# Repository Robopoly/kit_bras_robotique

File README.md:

# Kit Bras Robotique

The Kit Bras Robotique is a wireless robotic arm kit designed by [Robopoly](https://www.epfl.ch/campus/associations/robopoly/), the student makerspace of EPFL. A handheld controller with two joysticks drives a 3D printed arm with five servos.

Robopoly members buy the kit as separate parts and solder it themselves at the workshop, with help from the committee. It is an advanced kit: it uses small surface-mount components, so soldering experience is recommended but not required.

> **About the name:** this kit used to be called "Kit JIG". The boards, the assembly guides and parts of the code still use that name. It is now only used for another kit, with a wired controller and an Arduino Nano, which is in the [JIG repository](https://github.com/Robopoly/JIG). The mechanical arm is the same in both kits.

## Features

- Two boards, each with an ESP32-S3 module programmed over USB-C
- Wireless link between the controller and the arm (ESP-NOW, no WiFi network needed)
- Controller powered over USB-C or by an 18650 battery, with charger and battery protection on the board
- Arm board with 5 servo connectors (SG90 or MG90 servos) and a DC jack
- Optional Console extension: OLED screen, vibration motors, extra buttons and mini-games

## Repository contents

| Folder | Content |
|---|---|
| [`docs/`](docs) | Assembly guides, schematics, images |
| [`firmware/arm/`](firmware/arm) | Program of the arm board |
| [`firmware/controller_basic/`](firmware/controller_basic) | Program of the controller **without** the Console extension |
| [`firmware/controller_console/`](firmware/controller_console) | Program of the controller **with** the Console extension |
| [`firmware/tests/`](firmware/tests) | Test program used during assembly |
| [`hardware/`](hardware) | KiCad projects, Gerber files and bills of materials of both boards |
| [`mechanical/`](mechanical) | 3D printed parts (STL to print, STEP to modify) |
| [`tools/space_invaders_simulator/`](tools/space_invaders_simulator) | Space Invaders simulator for PC (Python) |

## Building the kit

The guides are in French for now. Do not move on until each test passes.

| Step | Guide | Test |
|---|---|---|
| 1. Controller board | [Controller guide](docs/controller_assembly_guide_v1.pdf) | The blue LED lights up, the board is detected over USB, `01_melody` plays a melody, both charger LEDs light up |
| 2. Arm board | [Arm board guide](docs/arm_assembly_guide_v1.pdf) | The LED lights up, the board is detected over USB |
| 3. Mechanical arm | [Mechanical guide](docs/arm_mechanical_guide_fsrm.pdf), pages 4 to 8 | |
| 4. Programs and pairing | [Programming](#programming) | The joysticks move the arm |

**Before you insert the battery, ask someone from the committee to check your controller.**

### Corrections to the guides

Some values in the soldering guides do not match the schematics. The values below come from the KiCad files:

| Board | Reference | In the guide | Use |
|---|---|---|---|
| Controller | R5, R6 | 1 kΩ | **10 kΩ** |
| Controller | R11 | 1 kΩ | **1.2 kΩ** |
| Controller | R18 | 1.2 kΩ | **1 kΩ** |
| Controller | C12 | 10 µF | **100 nF** |
| Controller | R16, R17 | 20 kΩ | **10 kΩ** |
| Controller | L1 | 10 µH | To be confirmed: 4.7 µH in the schematic, 10 µH on the PCB |
| Arm | R3 | 75 Ω | To be confirmed: 1 kΩ in the schematic, 75 Ω on the PCB |

If you have a doubt about a part, ask the committee.

### Which side of the board?

Both sides are used, and the guides do not always say which one.

| Board | Top side | Bottom side |
|---|---|---|
| Controller | U1, U6, U7, U8, Q1, L1, D5 to D8, C1 to C15, R1 to R6, R9 to R17, joysticks (U3, U4), buttons (S1, S2), buzzer (LS1) | U2 (ESP32), U9, D1, Q3, R7, R8, R18, USB-C (J1), switch (U5), battery holder (BT1) |
| Arm | U1, U2 (ESP32), D5, buttons (S1, S2), USB-C (J1), DC jack (J2), switch (U3), servo connectors (M1 to M5) | U9, D1, C1 to C10, R1 to R6 |

The components of the Console extension are J2, J3 and J4 (top), and M1, M2, Q2, Q4, D2, D3, R19 and R20 (bottom). The guide of this extension is not written yet. In the schematic and in the bill of materials, M1 and M2 are called J5 and J6.

### Mechanical arm

The mechanical guide was written for the Kit JIG workshops. Only pages 4 to 8 apply to this kit: the controller, the board and the wiring described on the other pages are different. Print these parts:

| File | Number in the guide | Quantity |
|---|---|---|
| `base` | 1 | 1 |
| `rotating_base` | 2 | 1 |
| `arm1` | 3 | 1 |
| `arm1_servo` | 4 | 1 |
| `arm2_servo` | 5 | 1 |
| `arm2` | 6 | 1 |
| `servo_support` | 7 | 1 |
| `gripper_base` | 8 | 1 |
| `rack` | 9 | **2** |
| `pinion` | 10 | 1 |

You also need the screws that come with the servos and M2x8 screws.

## Power

| Board | Switch | Positions |
|---|---|---|
| Controller | U5 | Cable (USB-C) or Batt (battery) |
| Arm | U3 | USB or Jack |

- **The DC jack of the arm goes straight to the servos: use a 5 V supply only.** The board has no protection against reversed polarity. *To be completed: which supply to use, and its polarity.*
- **Do not move the arm on USB power.** Five servos can draw several amps. Use the USB position to program the board, and the Jack position to move the arm.
- **When the arm is powered up, all the servos move straight to 90°.**

## Programming

### Download mode

If the board is not detected, or keeps connecting and disconnecting: hold **GPIO0**, press and release **RESET**, then release GPIO0. Press RESET again to start the program after the upload.

### Test program

Open [`01_melody`](firmware/tests/01_melody/01_melody.ino) with the [Arduino IDE](https://www.arduino.cc/en/software), with the **esp32 by Espressif Systems** package and the board **ESP32S3 Dev Module**. It plays a melody on the buzzer of the controller.

### Main programs

The main programs use [VS Code](https://code.visualstudio.com/) with the **PlatformIO IDE** extension. Open the folder of the program, plug in the board and click **Upload**.

| Board | Folder |
|---|---|
| Arm | [`firmware/arm/`](firmware/arm) |
| Controller without screen | [`firmware/controller_basic/`](firmware/controller_basic) |
| Controller with the Console extension | [`firmware/controller_console/`](firmware/controller_console) |

### Pairing the two boards

Each board needs the MAC address of the other one. The addresses in the code belong to the boards of the designer, so **you must replace them with yours**. Follow the steps in the [README of the arm program](firmware/arm/README.md#configuring-mac-addresses-required). If the Serial Monitor stays empty, see [Known issues](#known-issues).

### Controls

| Control | Action |
|---|---|
| Joystick 1 horizontal / vertical | Base / shoulder |
| Joystick 2 vertical / horizontal | Elbow / wrist |
| Joystick 2 button | Open or close the gripper |
| Joystick 1 button | `controller_basic`: back to the rest position. `controller_console`: back to the menu |

## Pinout

| Controller GPIO | Function |
|---|---|
| 1, 2, 5 | Joystick 1: vertical, horizontal, button |
| 3, 4, 6 | Joystick 2: vertical, horizontal, button |
| 8, 9 | Screen (J3): SDA, SCL |
| 10 | Battery voltage divided by 2 |
| 12 | Buzzer |
| 17, 18 | Vibration motors M1, M2 |
| 35 to 38, 39 to 42 | Extra buttons: J2, J4 |
| 0 | GPIO0 button |

| Arm GPIO | Function |
|---|---|
| 1 to 5 | Servos M1 to M5: base, shoulder, elbow, wrist, gripper |
| 0 | GPIO0 button |

Pinout of the servo connectors: pin 1 is the signal, pin 2 is 5 V and pin 3 is GND. The full wiring is in the schematics of the [controller](docs/controller_schematic_v1.pdf) and of the [arm board](docs/arm_schematic_v1.pdf).

## Known issues

These issues were found by reading the code and the PCB files. They have not been checked on a real board yet.

- **The Serial Monitor may stay empty.** Both boards only have the native USB of the ESP32-S3, and the programs do not enable it for the Serial Monitor. Workaround (it compiles, but is not tested on a board): add `-DARDUINO_USB_CDC_ON_BOOT=1` to `build_flags` in `platformio.ini`, then upload again.
- **The arm has no status LED.** The program uses GPIO 8, which is not connected. The LED D5 only shows that the board is powered. Ignore the status LED in the READMEs.
- **The joystick buttons may act when released**, because the code expects the opposite wiring. With `controller_basic`, the gripper may also move at startup.
- **The extra buttons of the Console extension are not used** by the programs yet.
- **"DOOM (Ecran)"** needs a separate screen whose program is not in this repository.
- **The README of the arm program** describes an external supply wired by hand. This board has a DC jack instead.

## To be completed

- Power supply of the arm
- Guide and part references of the Console extension
- Mechanical guide for this kit, print settings
- Memory variant of the ESP32-S3 modules
- Supplier references in the bills of materials
- Photos of the assembled kit: the board images above are renders, with several parts missing and not the real colors

## Hardware files

The KiCad projects are in [`hardware/controller/kicad/`](hardware/controller/kicad) and [`hardware/arm/kicad/`](hardware/arm/kicad). Open the `.kicad_pro` files with KiCad 10 or later. The Gerber files (`gerber_v1.zip`) were exported on 17 March 2026.

## Links

- [Kit page](https://www.epfl.ch/campus/associations/robopoly/kits/kit-jig-bras-robotique-telecommande/) (in French)
- [Robopoly](https://www.epfl.ch/campus/associations/robopoly/), workshop BM 9139, EPFL
- Contact: [robopoly@epfl.ch](mailto:robopoly@epfl.ch)

## License

Boards and programs designed by Sonny Basso for Robopoly.

- The three main programs (`firmware/arm`, `firmware/controller_basic` and `firmware/controller_console`) and the simulator (`tools/space_invaders_simulator`) are under the MIT license. See the `LICENSE` file in each folder.
- Everything else is published by Robopoly under the [Creative Commons Attribution-NonCommercial-ShareAlike 4.0](LICENSE.txt) license.

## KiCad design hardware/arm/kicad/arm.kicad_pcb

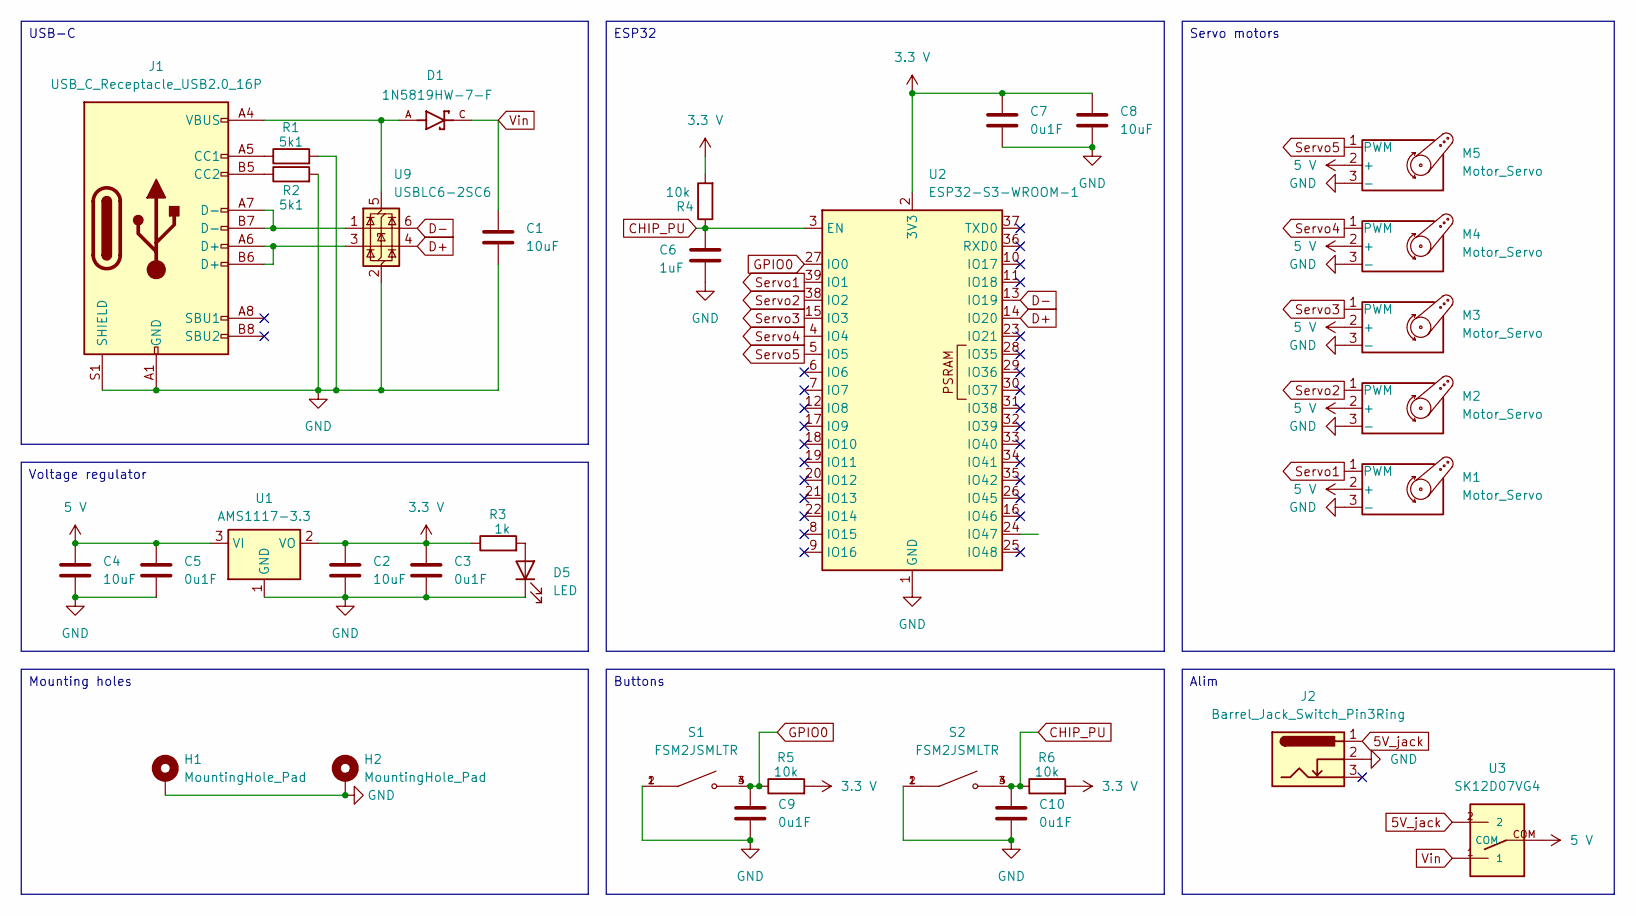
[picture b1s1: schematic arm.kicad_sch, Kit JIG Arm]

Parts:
C1, C2, C4, C8: 10uF; C_0805_2012Metric_Pad1.18x1.45mm_HandSolder
C3, C5, C7, C9, C10: 0u1F; C_0805_2012Metric_Pad1.18x1.45mm_HandSolder
C6: 1uF; C_0805_2012Metric_Pad1.18x1.45mm_HandSolder
D1: 1N5819HW-7-F; SOD3715X145N; PARTREV 18-2
D5: LED; LED_0805_2012Metric_Pad1.15x1.40mm_HandSolder
H1, H2: MountingHole_Pad; MountingHole_2.2mm_M2_ISO14580_Pad_TopBottom
J1: USB_C_Receptacle_USB2.0_16P; USB_C_Receptacle_HRO_TYPE-C-31-M-12
J2: Barrel_Jack_Switch_Pin3Ring; BarrelJack_Wuerth_6941xx301002
M1, M2, M3, M4, M5: Motor_Servo; PinHeader_1x03_P2.54mm_Vertical
R1, R2: 5k1; R_0805_2012Metric_Pad1.20x1.40mm_HandSolder
R3: 1k; R_0805_2012Metric_Pad1.20x1.40mm_HandSolder
R4, R5, R6: 10k; R_0805_2012Metric_Pad1.20x1.40mm_HandSolder
S1, S2: FSM2JSMLTR; SW_1571527-2; PARTREV V
U1: AMS1117-3.3; SOT-223-3_TabPin2
U2: ESP32-S3-WROOM-1
U3: SK12D07VG4
U9: USBLC6-2SC6; SOT-23-6

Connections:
3.3 V: C2.1, C3.1, C7.1, C8.1, R3.1, R4.2, R5.2, R6.2, U1.2 (VO), U2.2 (3V3)
5 V: C4.1, C5.1, M1.2 (+), M2.2 (+), M3.2 (+), M4.2 (+), M5.2 (+), U1.3 (VI), U3.COM
5V_jack: J2.1, U3.2
CHIP_PU: C6.1, C10.1, R4.1, R6.1, S2.3, S2.4, U2.3 (EN)
D+: U2.14 (IO20), U9.4 (I/O2)
D-: U2.13 (IO19), U9.6 (I/O1)
GND: C1.2, C2.2, C3.2, C4.2, C5.2, C6.2, C7.2, C8.2, C9.2, C10.2, D5.1 (K), H1.1, H2.1, J1.A1 (GND), J1.A12 (GND), J1.B1 (GND), J1.B12 (GND), J1.S1 (SHIELD), J2.2, M1.3 (-), M2.3 (-), M3.3 (-), M4.3 (-), M5.3 (-), R1.2, R2.2, S1.1, S1.2, S2.1, S2.2, U1.1 (GND), U2.1 (GND), U2.40 (GND), U2.41 (GND), U9.2 (GND)
GPIO0: C9.1, R5.1, S1.3, S1.4, U2.27 (IO0)
unnamed: D5.2 (A), R3.2
unnamed: J1.A5 (CC1), R1.1
unnamed: J1.B5 (CC2), R2.1
unnamed: J1.A6 (D+), J1.B6 (D+), U9.3 (I/O2)
unnamed: J1.A7 (D-), J1.B7 (D-), U9.1 (I/O1)
unnamed: D1.A, J1.A4 (VBUS), J1.A9 (VBUS), J1.B4 (VBUS), J1.B9 (VBUS), U9.5 (VBUS)
Servo1: M1.1 (PWM), U2.39 (IO1)
Servo2: M2.1 (PWM), U2.38 (IO2)
Servo3: M3.1 (PWM), U2.15 (IO3)
Servo4: M4.1 (PWM), U2.4 (IO4)
Servo5: M5.1 (PWM), U2.5 (IO5)
Vin: C1.1, D1.C, U3.1

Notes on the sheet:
Servo motors
Mounting holes
USB-C
Voltage regulator
ESP32
Buttons
Alim

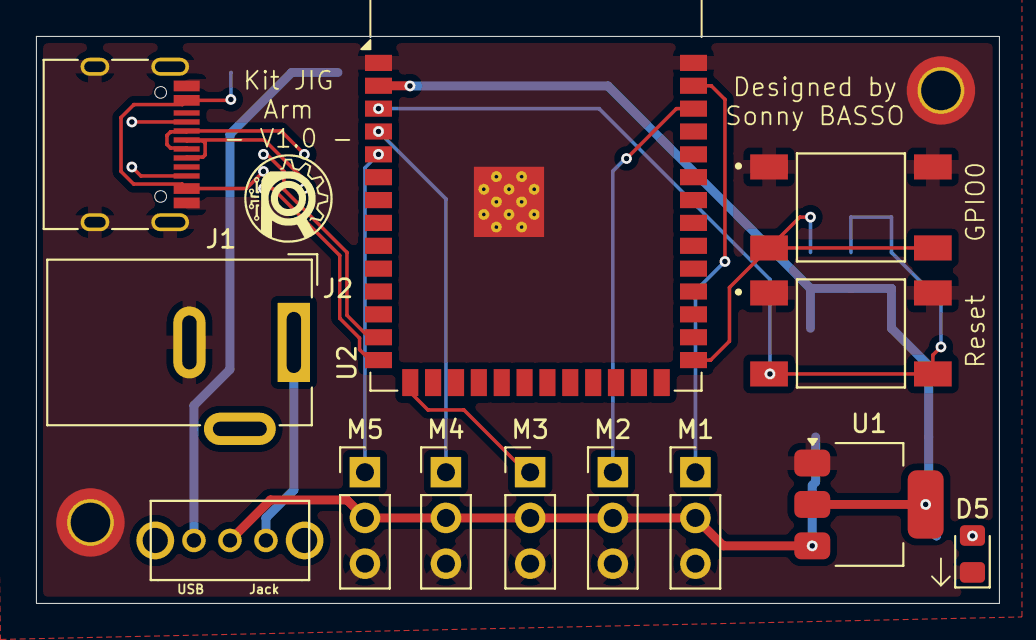
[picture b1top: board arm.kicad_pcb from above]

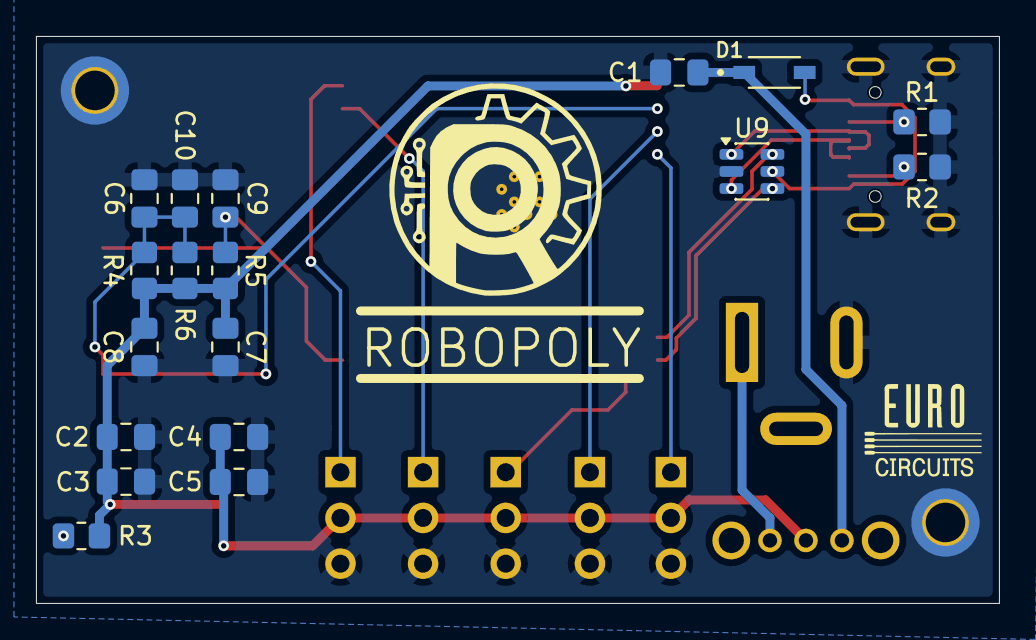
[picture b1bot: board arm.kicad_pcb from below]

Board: 2 copper layers, 53.5 x 31.5 mm, 33 parts (18 on the bottom side), 20 nets.

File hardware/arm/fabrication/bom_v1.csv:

"Reference","Qty","Value","DNP","Footprint","Datasheet"
"C1,C2,C4,C8","4","10uF","","Capacitor_SMD:C_0805_2012Metric_Pad1.18x1.45mm_HandSolder",""
"C3,C5,C7,C9,C10","5","0u1F","","Capacitor_SMD:C_0805_2012Metric_Pad1.18x1.45mm_HandSolder",""
"C6","1","1uF","","Capacitor_SMD:C_0805_2012Metric_Pad1.18x1.45mm_HandSolder",""
"D1","1","1N5819HW-7-F","","1N5819HW-7-F:SOD3715X145N",""
"D5","1","LED","","LED_SMD:LED_0805_2012Metric_Pad1.15x1.40mm_HandSolder",""
"J1","1","USB_C_Receptacle_USB2.0_16P","","Connector_USB:USB_C_Receptacle_HRO_TYPE-C-31-M-12","https://www.usb.org/sites/default/files/documents/usb_type-c.zip"
"J2","1","Barrel_Jack_Switch_Pin3Ring","","Connector_BarrelJack:BarrelJack_Wuerth_6941xx301002",""
"M1,M2,M3,M4,M5","5","Motor_Servo","","Connector_PinHeader_2.54mm:PinHeader_1x03_P2.54mm_Vertical","http://forums.parallax.com/uploads/attachments/46831/74481.png"
"R1,R2","2","5k1","","Resistor_SMD:R_0805_2012Metric_Pad1.20x1.40mm_HandSolder",""
"R3","1","1k","","Resistor_SMD:R_0805_2012Metric_Pad1.20x1.40mm_HandSolder",""
"R4,R5,R6","3","10k","","Resistor_SMD:R_0805_2012Metric_Pad1.20x1.40mm_HandSolder",""
"S1,S2","2","FSM2JSMLTR","","FSM2JSMLTR:SW_1571527-2",""
"U1","1","AMS1117-3.3","","Package_TO_SOT_SMD:SOT-223-3_TabPin2","http://www.advanced-monolithic.com/pdf/ds1117.pdf"
"U2","1","ESP32-S3-WROOM-1","","RF_Module:ESP32-S3-WROOM-1","https://www.espressif.com/sites/default/files/documentation/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"
"U3","1","SK12D07VG4","","SK12D07VG4:SK12D07VG4",""
"U9","1","USBLC6-2SC6","","Package_TO_SOT_SMD:SOT-23-6","https://www.st.com/resource/en/datasheet/usblc6-2.pdf"

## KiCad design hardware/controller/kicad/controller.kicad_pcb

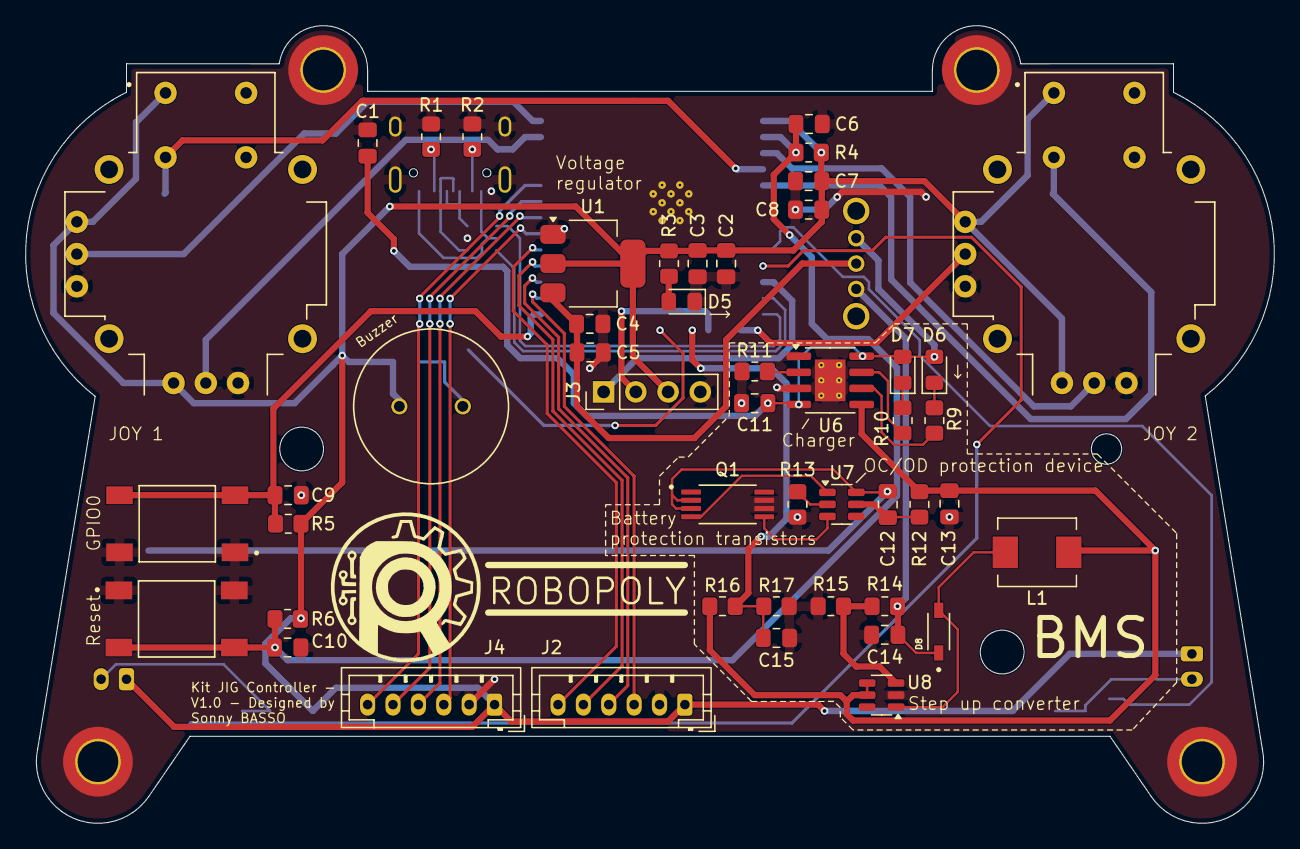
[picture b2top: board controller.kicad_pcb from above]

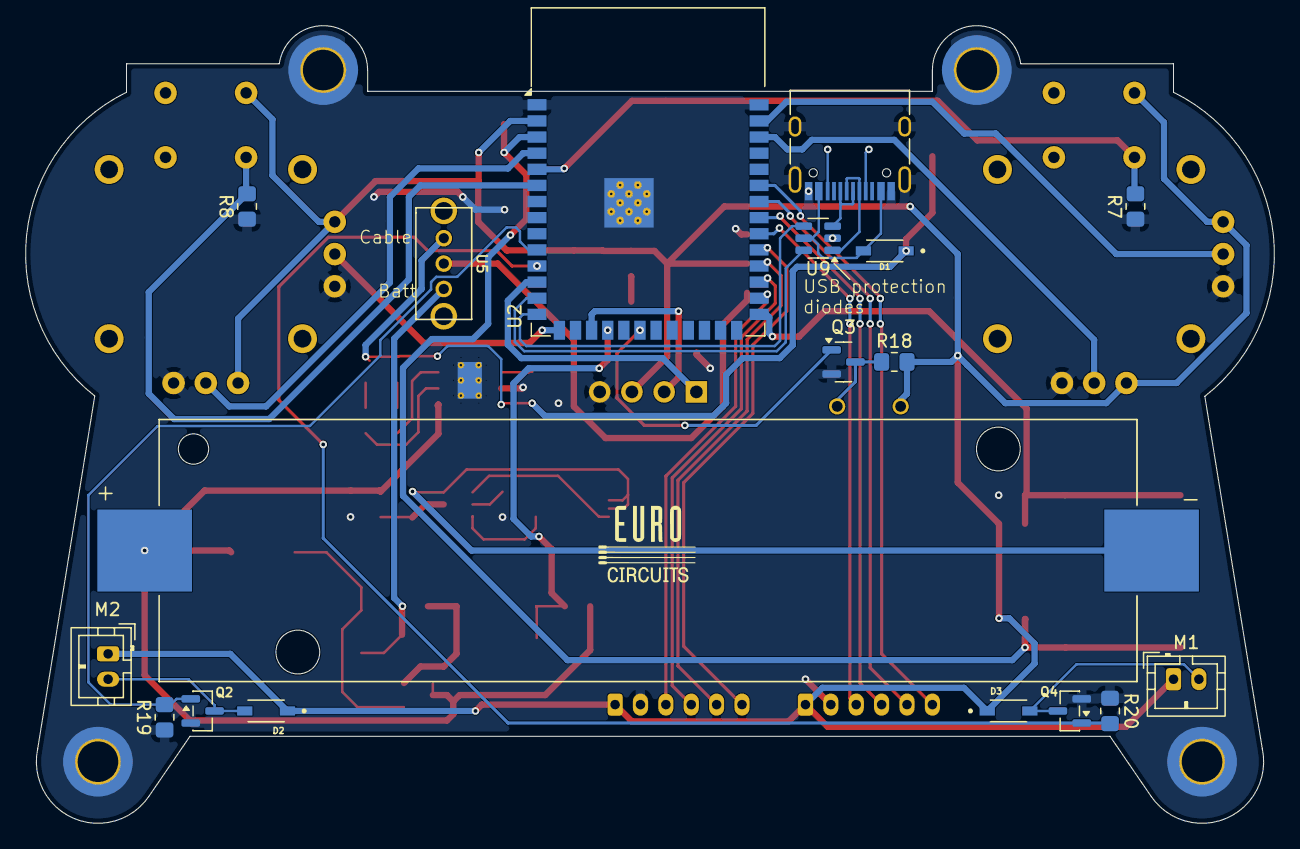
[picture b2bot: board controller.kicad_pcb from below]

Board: 2 copper layers, 98.4 x 62.8 mm, 70 parts (18 on the bottom side), 51 nets.

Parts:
BT1: 1042; BAT_1042
C1, C2, C4, C8, C11: 10uF; C_0805_2012Metric_Pad1.18x1.45mm_HandSolder
C3, C5, C7, C9, C10: 0u1F; C_0805_2012Metric_Pad1.18x1.45mm_HandSolder
C6: 1uF; C_0805_2012Metric_Pad1.18x1.45mm_HandSolder
C12, C15: 100nF; C_0805_2012Metric_Pad1.18x1.45mm_HandSolder
C13, C14: 22uF; C_0805_2012Metric_Pad1.18x1.45mm_HandSolder
D1, D2, D3, D8: 1N5819HW-7-F; SOD3715X145N
D5, D6, D7: LED; LED_0805_2012Metric_Pad1.15x1.40mm_HandSolder
H1, H2, H3, H4: MountingHole_Pad; MountingHole_3.2mm_M3_ISO14580_Pad_TopBottom
J1: USB_C_Receptacle_USB2.0_16P; USB_C_Receptacle_HRO_TYPE-C-31-M-12
J2, J4: Conn_01x06_Socket; JST_PH_B6B-PH-K_1x06_P2.00mm_Vertical
J3: I2C; PinHeader_1x04_P2.54mm_Vertical
L1: 10uH; inductor_48100SC
LS1: PS1240P02BT; XDCR_PS1240P02BT
M1, M2: Conn_01x02_Socket; JST_PH_B2B-PH-K_1x02_P2.00mm_Vertical
Q1: FS8205A; SOP65P640X120-8N
Q2, Q3, Q4: AO3400A; SOT-23
R1, R2: 5k1; R_0805_2012Metric_Pad1.20x1.40mm_HandSolder
R3, R9, R10, R13, R18: 1k; R_0805_2012Metric_Pad1.20x1.40mm_HandSolder
R4, R5, R6, R7, R8, R16, R17, R19, R20: 10k; R_0805_2012Metric_Pad1.20x1.40mm_HandSolder
R11: 1k2; R_0805_2012Metric_Pad1.20x1.40mm_HandSolder
R12: 100; R_0805_2012Metric_Pad1.20x1.40mm_HandSolder
R14: 22k; R_0805_2012Metric_Pad1.20x1.40mm_HandSolder
R15: 3k; R_0805_2012Metric_Pad1.20x1.40mm_HandSolder
S1, S2: FSM2JSMLTR; SW_1571527-2
U1: AMS1117-3.3; SOT-223-3_TabPin2
U2: ESP32-S3-WROOM-1
U3, U4: COM-09032; XDCR_COM-09032
U5: SK12D07VG4
U6: TP4056-42-ESOP8; SOIC-8-1EP_3.9x4.9mm_P1.27mm_EP2.41x3.3mm_ThermalVias
U7: DW01A; SOT-23-6
U8: MT3608; SOT-23-6
U9: USBLC6-2SC6; SOT-23-6

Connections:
3.3 V: C2.1, C3.1, C7.1, C8.1, D2.C, D3.C, J2.1, J3.3, J4.1, LS1.1, M1.1, M2.1, R3.1, R4.2, R5.2, R6.2, R18.2, U1.2 (VO), U2.2 (3V3), U3.B1A (SEL+), U3.H1 (H+), U3.V1 (V+), U4.B1A (SEL+), U4.H1 (H+), U4.V1 (V+)
5 V: C4.1, C5.1, U1.3 (VI), U5.COM
/BMS/Bat+: BT1.P, C13.1, L1.1, R12.1, R16.1, U6.5 (BAT), U8.4 (EN), U8.5 (IN)
ADC_Vbat: C15.1, R16.2, R17.1, U2.18 (IO10)
B1a: J2.3, U2.28 (IO35)
B1b: J2.4, U2.29 (IO36)
B1c: J2.5, U2.30 (IO37)
B1d: J2.6, U2.31 (IO38)
B2a: J4.3, U2.32 (IO39)
B2b: J4.4, U2.33 (IO40)
B2c: J4.5, U2.34 (IO41)
B2d: J4.6, U2.35 (IO42)
Buzzer: Q3.1 (G), U2.20 (IO12)
CHIP_PU: C6.1, C10.1, R4.1, R6.1, S2.3, S2.4, U2.3 (EN)
D+: U2.14 (IO20), U9.4 (I/O2)
D-: U2.13 (IO19), U9.6 (I/O1)
GND: C1.2, C2.2, C3.2, C4.2, C5.2, C6.2, C7.2, C8.2, C9.2, C10.2, C11.2, C13.2, C14.2, C15.2, D5.1 (K), H1.1, H2.1, H3.1, H4.1, J1.A1 (GND), J1.A12 (GND), J1.B1 (GND), J1.B12 (GND), J1.S1 (SHIELD), J2.2, J3.4, J4.2, Q1.6, Q1.7, Q2.2 (S), Q3.2 (S), Q4.2 (S), R1.2, R2.2, R7.1, R8.1, R11.1, R13.1, R15.2, R17.2, R19.1, R20.1, S1.1, S1.2, S2.1, S2.2, U1.1 (GND), U2.1 (GND), U2.40 (GND), U2.41 (GND), U3.H3 (H-), U3.V3 (V-), U4.H3 (H-), U4.V3 (V-), U6.1 (TEMP), U6.3 (GND), U6.9 (EPAD), U8.2 (GND), U9.2 (GND)
GPIO0: C9.1, R5.1, S1.3, S1.4, U2.27 (IO0)
Joy1_H: U2.38 (IO2), U3.H2 (H)
Joy1_S: R7.2, U2.5 (IO5), U3.B2A (SEL-)
Joy1_V: U2.39 (IO1), U3.V2 (V)
Joy2_H: U2.4 (IO4), U4.H2 (H)
Joy2_S: R8.2, U2.6 (IO6), U4.B2A (SEL-)
Joy2_V: U2.15 (IO3), U4.V2 (V)
M1: Q2.1 (G), R19.2, U2.10 (IO17)
M2: Q4.1 (G), R20.2, U2.11 (IO18)
unnamed: D5.2 (A), R3.2
unnamed: D6.1 (K), R9.2
unnamed: D7.1 (K), R10.2
unnamed: J1.A5 (CC1), R1.1
unnamed: J1.B5 (CC2), R2.1
unnamed: J1.A6 (D+), J1.B6 (D+), U9.3 (I/O2)
unnamed: J1.A7 (D-), J1.B7 (D-), U9.1 (I/O1)
unnamed: D2.A, M2.2, Q2.3 (D)
unnamed: D3.A, M1.2, Q4.3 (D)
unnamed: LS1.2, Q3.3 (D), R18.1
unnamed: R11.2, U6.2 (PROG)
unnamed: R10.1, U6.7 (~CHRG)
unnamed: R9.1, U6.6 (~STDBY)
unnamed: R13.2, U7.2 (CS)
unnamed: BT1.N, C12.2, Q1.2, Q1.3, U7.6 (GND)
unnamed: Q1.5, U7.3 (OC)
unnamed: Q1.4, U7.1 (OD)
unnamed: C12.1, R12.2, U7.5 (VCC)
unnamed: R14.2, R15.1, U8.3 (FB)
unnamed: D8.A, L1.2, U8.1 (SW)
unnamed: D1.A, J1.A4 (VBUS), J1.A9 (VBUS), J1.B4 (VBUS), J1.B9 (VBUS), U9.5 (VBUS)
SCL: J3.2, U2.17 (IO9)
SDA: J3.1, U2.12 (IO8)
Vbat: C14.1, D8.C, R14.1, U5.2
Vin: C1.1, C11.1, D1.C, D6.2 (A), D7.2 (A), U5.1, U6.4 (V_{CC}), U6.8 (CE)

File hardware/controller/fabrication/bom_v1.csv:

"Reference","Qty","Value","DNP","Footprint","Datasheet"
"BT1","1","1042","","1042:BAT_1042",""
"C1,C2,C4,C8,C11","5","10uF","","Capacitor_SMD:C_0805_2012Metric_Pad1.18x1.45mm_HandSolder",""
"C3,C5,C7,C9,C10","5","0u1F","","Capacitor_SMD:C_0805_2012Metric_Pad1.18x1.45mm_HandSolder",""
"C6","1","1uF","","Capacitor_SMD:C_0805_2012Metric_Pad1.18x1.45mm_HandSolder",""
"C12,C15","2","100nF","","Capacitor_SMD:C_0805_2012Metric_Pad1.18x1.45mm_HandSolder",""
"C13,C14","2","22uF","","Capacitor_SMD:C_0805_2012Metric_Pad1.18x1.45mm_HandSolder",""
"D1,D2,D3,D8","4","1N5819HW-7-F","","1N5819HW-7-F:SOD3715X145N",""
"D5,D6,D7","3","LED","","LED_SMD:LED_0805_2012Metric_Pad1.15x1.40mm_HandSolder",""
"J1","1","USB_C_Receptacle_USB2.0_16P","","Connector_USB:USB_C_Receptacle_HRO_TYPE-C-31-M-12","https://www.usb.org/sites/default/files/documents/usb_type-c.zip"
"J2,J4","2","Conn_01x06_Socket","","Connector_JST:JST_PH_B6B-PH-K_1x06_P2.00mm_Vertical",""
"J3","1","I2C","","Connector_PinHeader_2.54mm:PinHeader_1x04_P2.54mm_Vertical",""
"J5,J6","2","Conn_01x02_Socket","","Connector_JST:JST_PH_B2B-PH-K_1x02_P2.00mm_Vertical",""
"L1","1","4u7H","","Kit_JIG_inductor:inductor_48100SC",""
"LS1","1","PS1240P02BT","","PS1240P02BT:XDCR_PS1240P02BT",""
"Q1","1","FS8205A","","FS8205A:SOP65P640X120-8N",""
"Q2,Q3,Q4","3","AO3400A","","Package_TO_SOT_SMD:SOT-23","http://www.aosmd.com/pdfs/datasheet/AO3400A.pdf"
"R1,R2","2","5k1","","Resistor_SMD:R_0805_2012Metric_Pad1.20x1.40mm_HandSolder",""
"R3,R9,R10,R13,R18","5","1k","","Resistor_SMD:R_0805_2012Metric_Pad1.20x1.40mm_HandSolder",""
"R4,R5,R6,R7,R8,R16,R17,R19,R20","9","10k","","Resistor_SMD:R_0805_2012Metric_Pad1.20x1.40mm_HandSolder",""
"R11","1","1k2","","Resistor_SMD:R_0805_2012Metric_Pad1.20x1.40mm_HandSolder",""
"R12","1","100","","Resistor_SMD:R_0805_2012Metric_Pad1.20x1.40mm_HandSolder",""
"R14","1","22k","","Resistor_SMD:R_0805_2012Metric_Pad1.20x1.40mm_HandSolder",""
"R15","1","3k","","Resistor_SMD:R_0805_2012Metric_Pad1.20x1.40mm_HandSolder",""
"S1,S2","2","FSM2JSMLTR","","FSM2JSMLTR:SW_1571527-2",""
"U1","1","AMS1117-3.3","","Package_TO_SOT_SMD:SOT-223-3_TabPin2","http://www.advanced-monolithic.com/pdf/ds1117.pdf"
"U2","1","ESP32-S3-WROOM-1","","RF_Module:ESP32-S3-WROOM-1","https://www.espressif.com/sites/default/files/documentation/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"
"U3,U4","2","COM-09032","","COM-09032:XDCR_COM-09032",""
"U5","1","SK12D07VG4","","SK12D07VG4:SK12D07VG4",""
"U6","1","TP4056-42-ESOP8","","Package_SO:SOIC-8-1EP_3.9x4.9mm_P1.27mm_EP2.41x3.3mm_ThermalVias","https://www.lcsc.com/datasheet/lcsc_datasheet_2410121619_TOP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"
"U7","1","DW01A","","Package_TO_SOT_SMD:SOT-23-6","https://hmsemi.com/downfile/DW01A.PDF"
"U8","1","MT3608","","Package_TO_SOT_SMD:SOT-23-6","https://www.olimex.com/Products/Breadboarding/BB-PWR-3608/re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"
"U9","1","USBLC6-2SC6","","Package_TO_SOT_SMD:SOT-23-6","https://www.st.com/resource/en/datasheet/usblc6-2.pdf"

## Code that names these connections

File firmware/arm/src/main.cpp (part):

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// ========== CONFIGURATION ==========

// Pins des servomoteurs (GPIO 1 à 5)
#define SERVO1_PIN 1  // Base
#define SERVO2_PIN 2  // Épaule
#define SERVO3_PIN 3  // Coude  
#define SERVO4_PIN 4  // Poignet
#define SERVO5_PIN 5  // Pince

// Pin LED d'état
#define STATUS_LED_PIN 8
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  lastCommandReceived = millis();
  
  // Appliquer les nouvelles positions
  targetPositions[0] = constrain(cmd->servo1, 0, 180);
  targetPositions[1] = constrain(cmd->servo2, 0, 180);
  targetPositions[2] = constrain(cmd->servo3, 0, 180);
  targetPositions[3] = constrain(cmd->servo4, 0, 180);
  targetPositions[4] = constrain(cmd->servo5, 0, 180);
  
  if (emergencyStop) {
    setEmergencyStop(false);
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
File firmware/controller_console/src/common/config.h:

#ifndef CONFIG_H
#define CONFIG_H

#include <Arduino.h>
#include <Wire.h>
#include <Adafruit_GFX.h>
#include <Adafruit_SSD1306.h>

// === Configuration écran OLED ===
#define SCREEN_WIDTH 128
#define SCREEN_HEIGHT 64
extern Adafruit_SSD1306 display;

// === Broches joystick ===
#define JOYSTICK_Y_PIN 1   // GPIO1 (JOY1_V) - axe Y pour mouvement menu
#define JOYSTICK_X_PIN 3   // GPIO3 (JOY2_V) - axe X pour mouvement horizontal
#define JOY1_H_PIN 2       // GPIO2 (JOY1_H) - axe horizontal du joystick 1
#define JOYSTICK_BTN_PIN 6 // GPIO6 (JOY2_BTN) - bouton du 2e joystick
#define JOYSTICK_DEADZONE 300

// === Configuration joystick Pong ===
#define JOY1_V 1   // GPIO1
#define JOY2_V 3   // GPIO3
#define JOY2_H 4   // GPIO4 - Joystick 2 Horizontal
#define JOY1_BTN 5 // GPIO5
#define JOY2_BTN 6 // GPIO6
#define JOY1_BTN_PIN 5 // GPIO5 - alias pour compatibilité Snake

// === Batterie ADC ===
// Le diviseur de tension divise par 2, VBAT_ADC_PIN lit la moitié de la tension
#define VBAT_ADC_PIN 10 // GPIO10 - entrée ADC pour mesurer la tension batterie via diviseur

// Variables pour calibration joystick
extern int joystickCenter;

// États du système
enum GameState {
  MENU,
  PONG,
  SPACE_INVADERS,
  PACMAN,
  SNAKE,
  ROBOT_CONTROL,
  DOOM,
  DOOM_REMOTE   /* controller mode: streams inputs to Waveshare via ESP-NOW */
};

extern GameState currentState;
extern bool requestReturnToMenu;

// Fonctions communes
void initDisplay();
void initJoystick();

#endif
